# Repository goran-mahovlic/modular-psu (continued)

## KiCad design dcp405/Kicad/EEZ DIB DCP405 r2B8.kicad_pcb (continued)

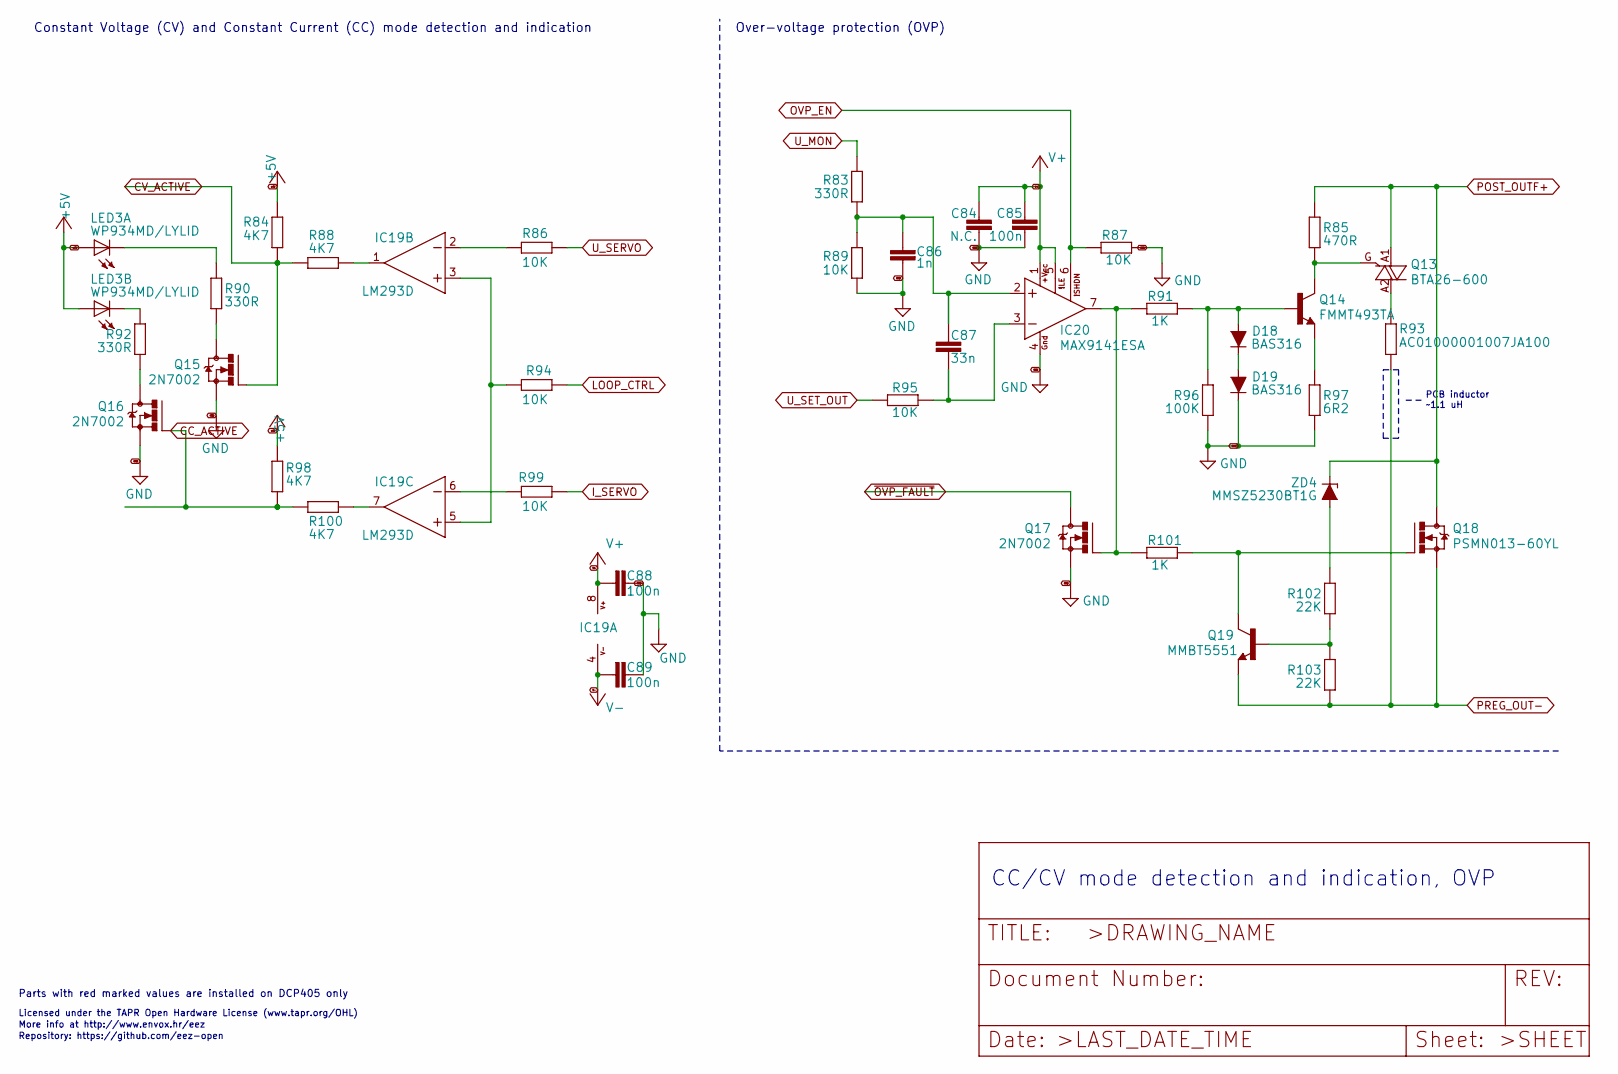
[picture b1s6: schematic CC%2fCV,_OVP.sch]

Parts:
C84: N.C.; C0805
C85, C88, C89: 100n; C0603
C86: 1n; C0805
C87: 33n; C0805
D18, D19: BAS316; SOD323-R
IC19: LM293D; SOIC127P600X173-8N
IC20: MAX9141ESA; SOIC127P600X173-8N
LED3: WP934MD/LYLID; WP934MD
Q13: BTA26-600; TOP3_TRIAC_NOHOLE
Q14: FMMT493TA; SOT23-BEC
Q15, Q16, Q17: 2N7002; SOT103P240X110-3N
Q18: PSMN013-60YL; SOT669
Q19: MMBT5551; SOT23-BEC
R83, R90, R92: 330R; R0805
R84, R88, R98, R100: 4K7; R0805
R85: 470R; R0805
R86, R87, R89, R94, R95, R99: 10K; R0805
R91, R101: 1K; R0805
R93: AC01000001007JA100; 0411_15
R96: 100K; R0805
R97: 6R2; R0805
R102, R103: 22K; R0805
ZD4: MMSZ5230BT1G; SOD123

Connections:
+5V: LED3.BA (A), LED3.TA (A), R84.2, R98.2; also elsewhere on the board
CC_ACTIVE: Q16.1 (G), R98.1, R100.2; also elsewhere on the board
CV_ACTIVE: Q15.1 (G), R84.1, R88.2; also elsewhere on the board
GND: C84.2, C85.1, C86.1, C88.1, C89.1, D19.C, IC20.4 (GND), Q15.2 (S), Q16.2 (S), Q17.2 (S), R87.1, R89.2, R96.1, R97.1; also elsewhere on the board
I_SERVO: R99.1; also elsewhere on the board
LOOP_CTRL: R94.2; also elsewhere on the board
unnamed: C86.2, C87.1, IC20.2 (+IN), R83.2, R89.1
unnamed: C87.2, IC20.3 (-IN), R95.2
unnamed: D18.A, Q14.B, R91.1, R96.2
unnamed: D18.C, D19.A
unnamed: IC19.1 (OUT), R88.1
unnamed: IC19.2 (-IN), R86.2
unnamed: IC19.3 (+IN), IC19.5 (+IN), R94.1
unnamed: IC19.6 (-IN), R99.2
unnamed: IC19.7 (OUT), R100.1
unnamed: IC20.7 (OUT), Q17.1 (G), R91.2, R101.2
unnamed: LED3.BC (C), R92.2
unnamed: LED3.TC (C), R90.1
unnamed: Q13.A2, R93.2
unnamed: Q13.G, Q14.C, R85.1
unnamed: Q14.E, R97.2
unnamed: Q15.3 (D), R90.2
unnamed: Q16.3 (D), R92.1
unnamed: Q18.4 (G), Q19.C, R101.1
unnamed: Q19.B, R102.1, R103.2
unnamed: R102.2, ZD4.A
OVP_EN: IC20.6 (~SHDN), R87.2; also elsewhere on the board
POST_OUTF+: Q13.A1, Q18.MB (D), R85.2, ZD4.C; also elsewhere on the board
PREG_OUT-: Q18.1 (S), Q18.2 (S), Q18.3 (S), Q19.E, R93.1, R103.1; also elsewhere on the board
U_MON: R83.1; also elsewhere on the board
U_SERVO: R86.1; also elsewhere on the board
U_SET_OUT: R95.1; also elsewhere on the board
V+: C84.1, C85.2, C88.2, IC19.8 (V+), IC20.1 (+VCC), IC20.5 (~LE); also elsewhere on the board
V-: C89.2, IC19.4 (V-); also elsewhere on the board
~OVP_FAULT: Q17.3 (D); also elsewhere on the board

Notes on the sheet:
Licensed under the TAPR Open Hardware License (www.tapr.org/OHL)
Repository: https://github.com/eez-open
More info at http://www.envox.hr/eez
CC/CV mode detection and indication, OVP
Constant Voltage (CV) and Constant Current (CC) mode detection and indication
Over-voltage protection (OVP)
PCB inductor ~~1.1 uH ~
Parts with red marked values are installed on DCP405 only

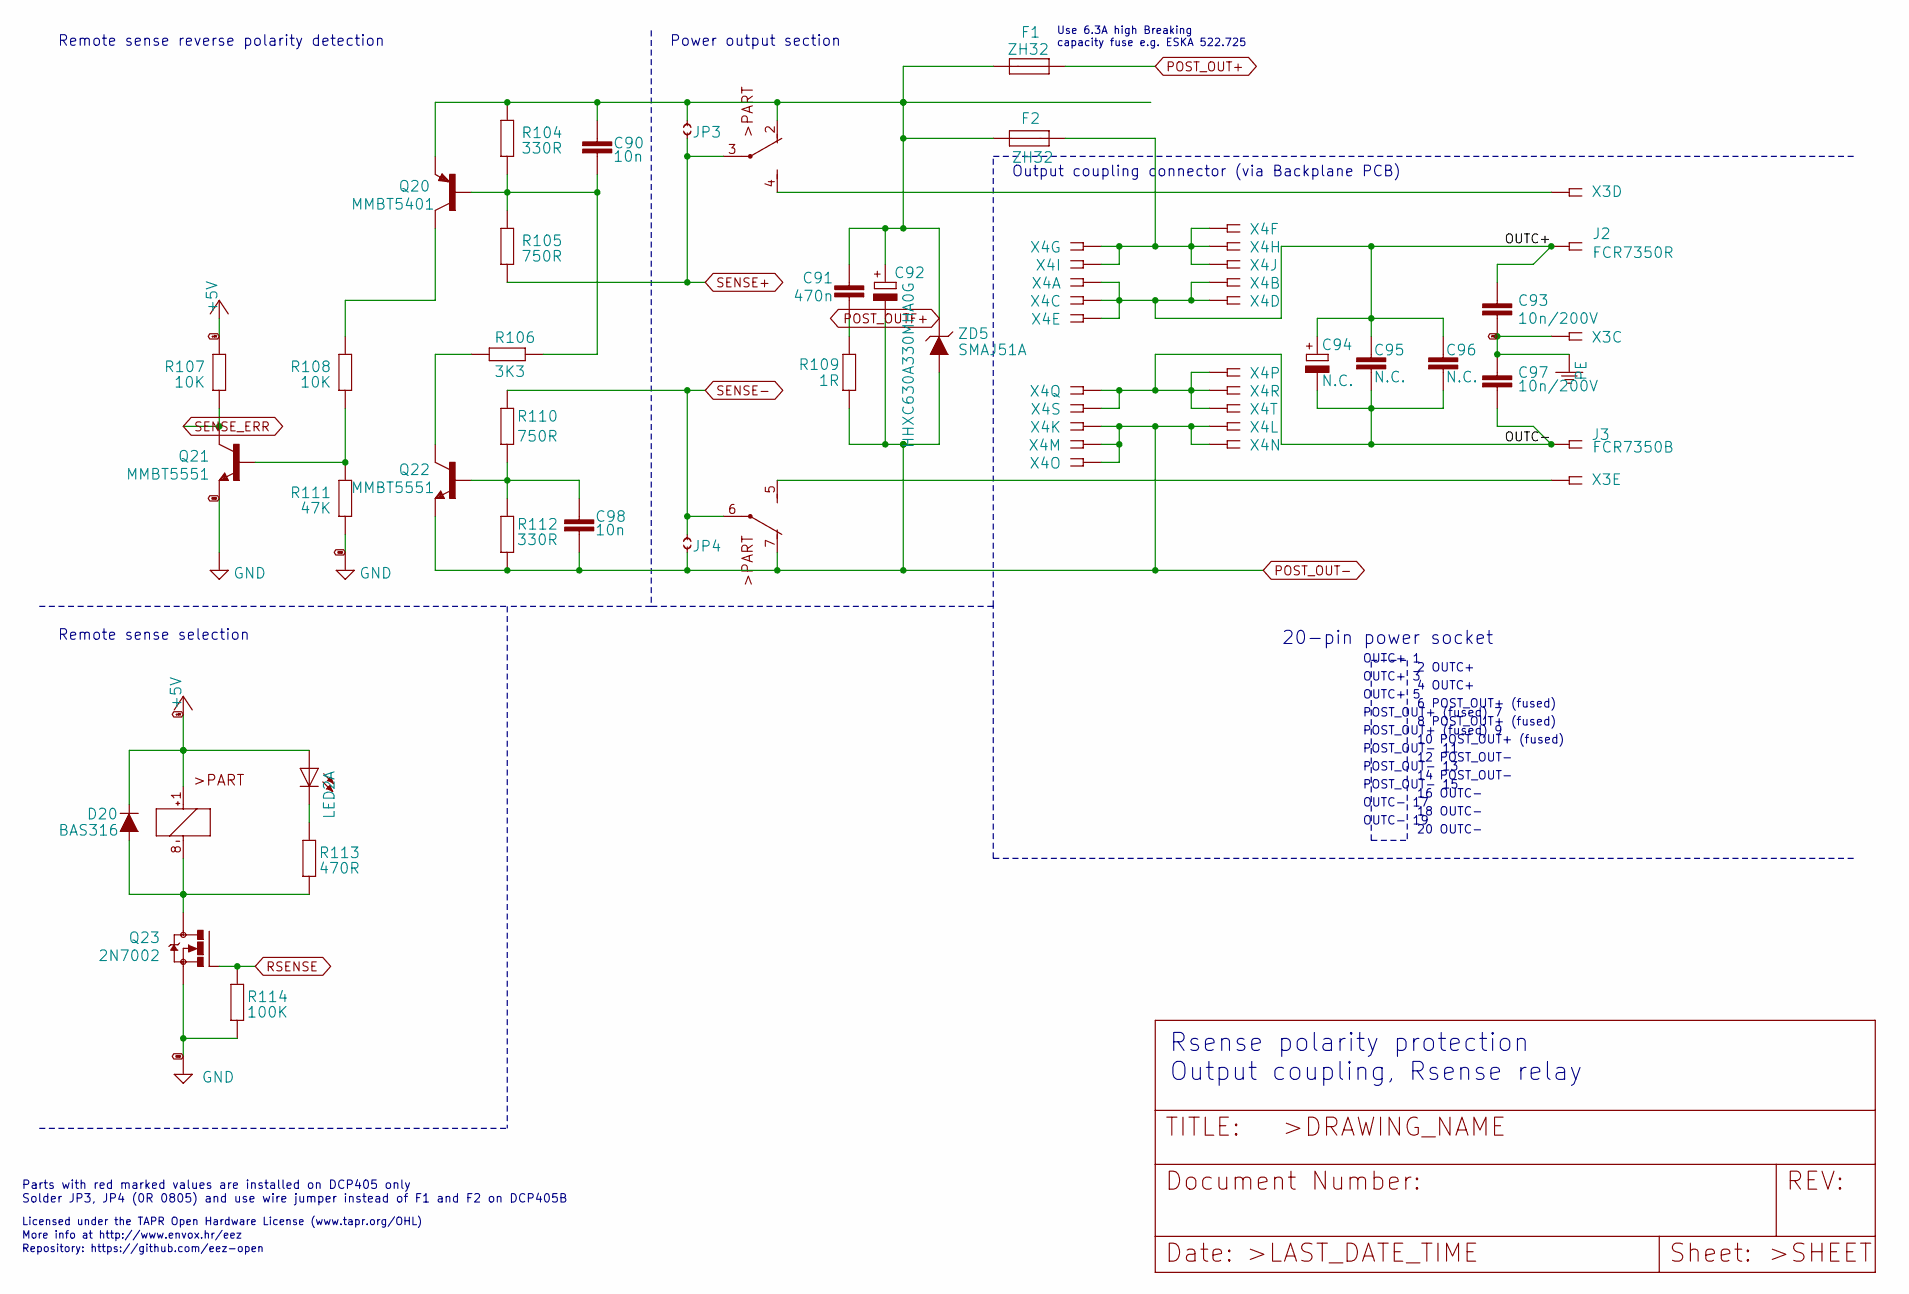
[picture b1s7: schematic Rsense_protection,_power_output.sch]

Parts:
C90, C98: 10n; C0805
C91: 470n; C0805
C92: HHXC630A330MHA0G; CAPAE830X1050N
C93, C97: 10n/200V; C1206
C94: N.C.; ECAP2_5
C95, C96: N.C.; C0805
D20: BAS316; SOD323-R
F1, F2: ZH32
J2: FCR7350R; S16N-PC
J3: FCR7350B; S16N-PC
JP3, JP4: JP2-CUT-0805; R_0805
K1: G6K-2F-5DC; G6K-2F
LED2: WP934MD/2LID; WP934MD
Q20: MMBT5401; SOT23-BEC
Q21, Q22: MMBT5551; SOT23-BEC
Q23: 2N7002; SOT103P240X110-3N
R104, R112: 330R; R0805
R105, R110: 750R; R0805
R106: 3K3; R0805
R107, R108: 10K; R0805
R109: 1R; R1206
R111: 47K; R0805
R113: 470R; R0805
R114: 100K; R0805
X3: 691322110005; MC1,5_5-G-3,5
X4: DS1024-2*10R0; SSW-110-02-T-D-RA
ZD5: SMAJ51A; DO214AA

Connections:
+5V: D20.C, K1.1 (+), LED2.TA (A), R107.2; also elsewhere on the board
/Rsense protection, power output/OUTC+: C93.1, C94.+, C95.1, C96.1, J2.1, J2.NC1, J2.NC2, J2.NC3, J2.NC4, X4.1, X4.2, X4.3, X4.4, X4.5
/Rsense protection, power output/OUTC-: C94.-, C95.2, C96.2, C97.2, J3.1, J3.NC1, J3.NC2, J3.NC3, J3.NC4, X4.16, X4.17, X4.18, X4.19, X4.20
GND: Q21.E, Q23.2 (S), R111.1, R114.1; also elsewhere on the board
unnamed: C90.2, Q20.B, R104.1, R105.2, R106.2
unnamed: C91.2, R109.2
unnamed: C98.1, Q22.B, R110.1, R112.2
unnamed: D20.A, K1.8 (-), Q23.3 (D), R113.1
unnamed: F2.2, X4.6, X4.7, X4.8, X4.9, X4.10
unnamed: K1.4 (S), X3.4
unnamed: K1.5 (S), X3.5
unnamed: LED2.TC (C), R113.2
unnamed: Q20.C, R108.2
unnamed: Q21.B, R108.1, R111.2
unnamed: Q22.C, R106.1
PE: C93.2, C97.1, X3.3; also elsewhere on the board
POST_OUT+: F1.1; also elsewhere on the board
POST_OUT-: C92.-, C98.2, JP4.1, K1.7 (O), Q22.E, R109.1, R112.1, X4.11, X4.12, X4.13, X4.14, X4.15, ZD5.A; also elsewhere on the board
POST_OUTF+: C90.1, C91.1, C92.+, F1.2, F2.1, JP3.2, K1.2 (O), Q20.E, R104.2, ZD5.C; also elsewhere on the board
RSENSE: Q23.1 (G), R114.2; also elsewhere on the board
SENSE+: JP3.1, K1.3, R105.1; also elsewhere on the board
SENSE-: JP4.2, K1.6, R110.2; also elsewhere on the board
SENSE_ERR: Q21.C, R107.1; also elsewhere on the board

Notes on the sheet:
Rsense polarity protection Output coupling, Rsense relay
Licensed under the TAPR Open Hardware License (www.tapr.org/OHL)
Repository: https://github.com/eez-open
More info at http://www.envox.hr/eez
Remote sense reverse polarity detection
Remote sense selection
POST_OUT+ (fused) 7
16 OUTC-
6 POST_OUT+ (fused)
20-pin power socket
10 POST_OUT+ (fused)
POST_OUT+ (fused) 9
2 OUTC+
12 POST_OUT-
OUTC+ 1
POST_OUT- 11
8 POST_OUT+ (fused)
OUTC+ 5
OUTC- 19
4 OUTC+
OUTC- 17
20 OUTC-
OUTC+ 3
14 POST_OUT-
POST_OUT- 15
POST_OUT- 13
18 OUTC-
Output coupling connector (via Backplane PCB)
Power output section
Use 6.3A high Breaking capacity fuse e.g. ESKA 522.725
Parts with red marked values are installed on DCP405 only Solder JP3, JP4 (0R 0805) and use wire jumper instead of F1 and F2 on DCP405B

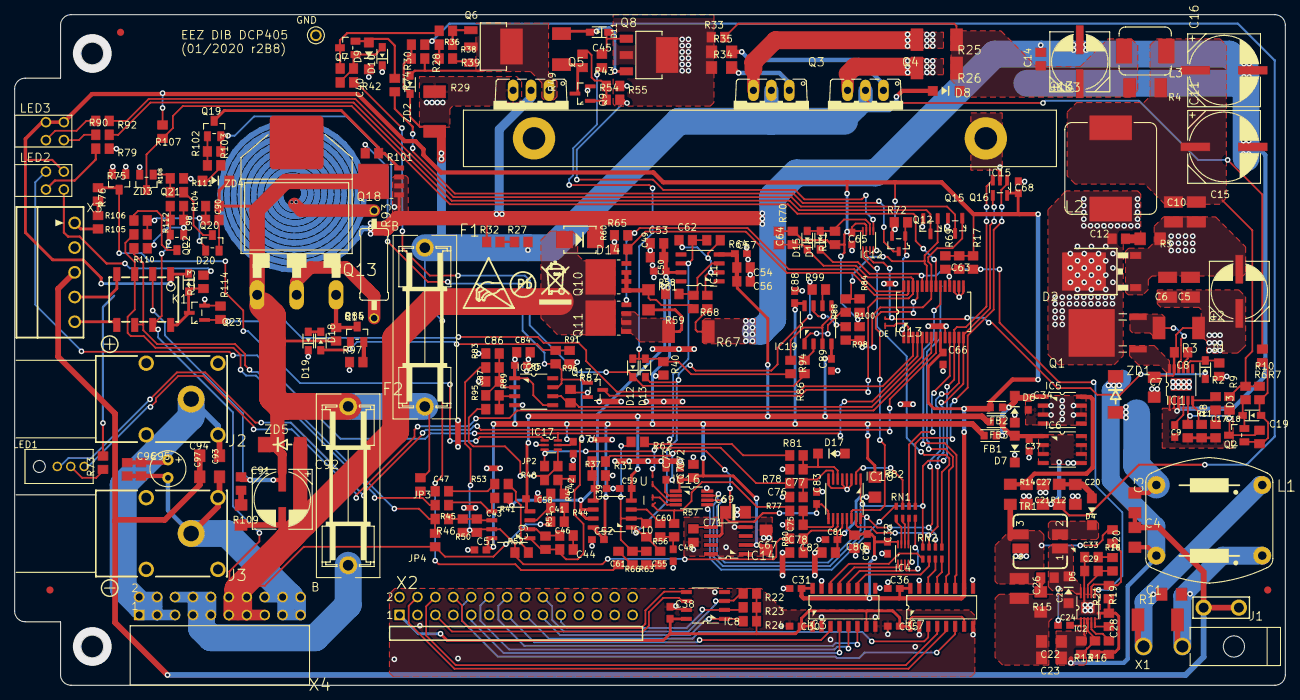
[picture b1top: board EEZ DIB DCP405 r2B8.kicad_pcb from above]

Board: 2 copper layers, 180.0 x 95.0 mm, 324 parts (0 on the bottom side), 194 nets.

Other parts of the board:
EEZ_SIGNATURE: SIGNATURESMALL; SIGNATURE_5MM
U$1: RECYCLE_BIN1_8
U$6: ESD_SYMBOL
U$7: PB_SMALL

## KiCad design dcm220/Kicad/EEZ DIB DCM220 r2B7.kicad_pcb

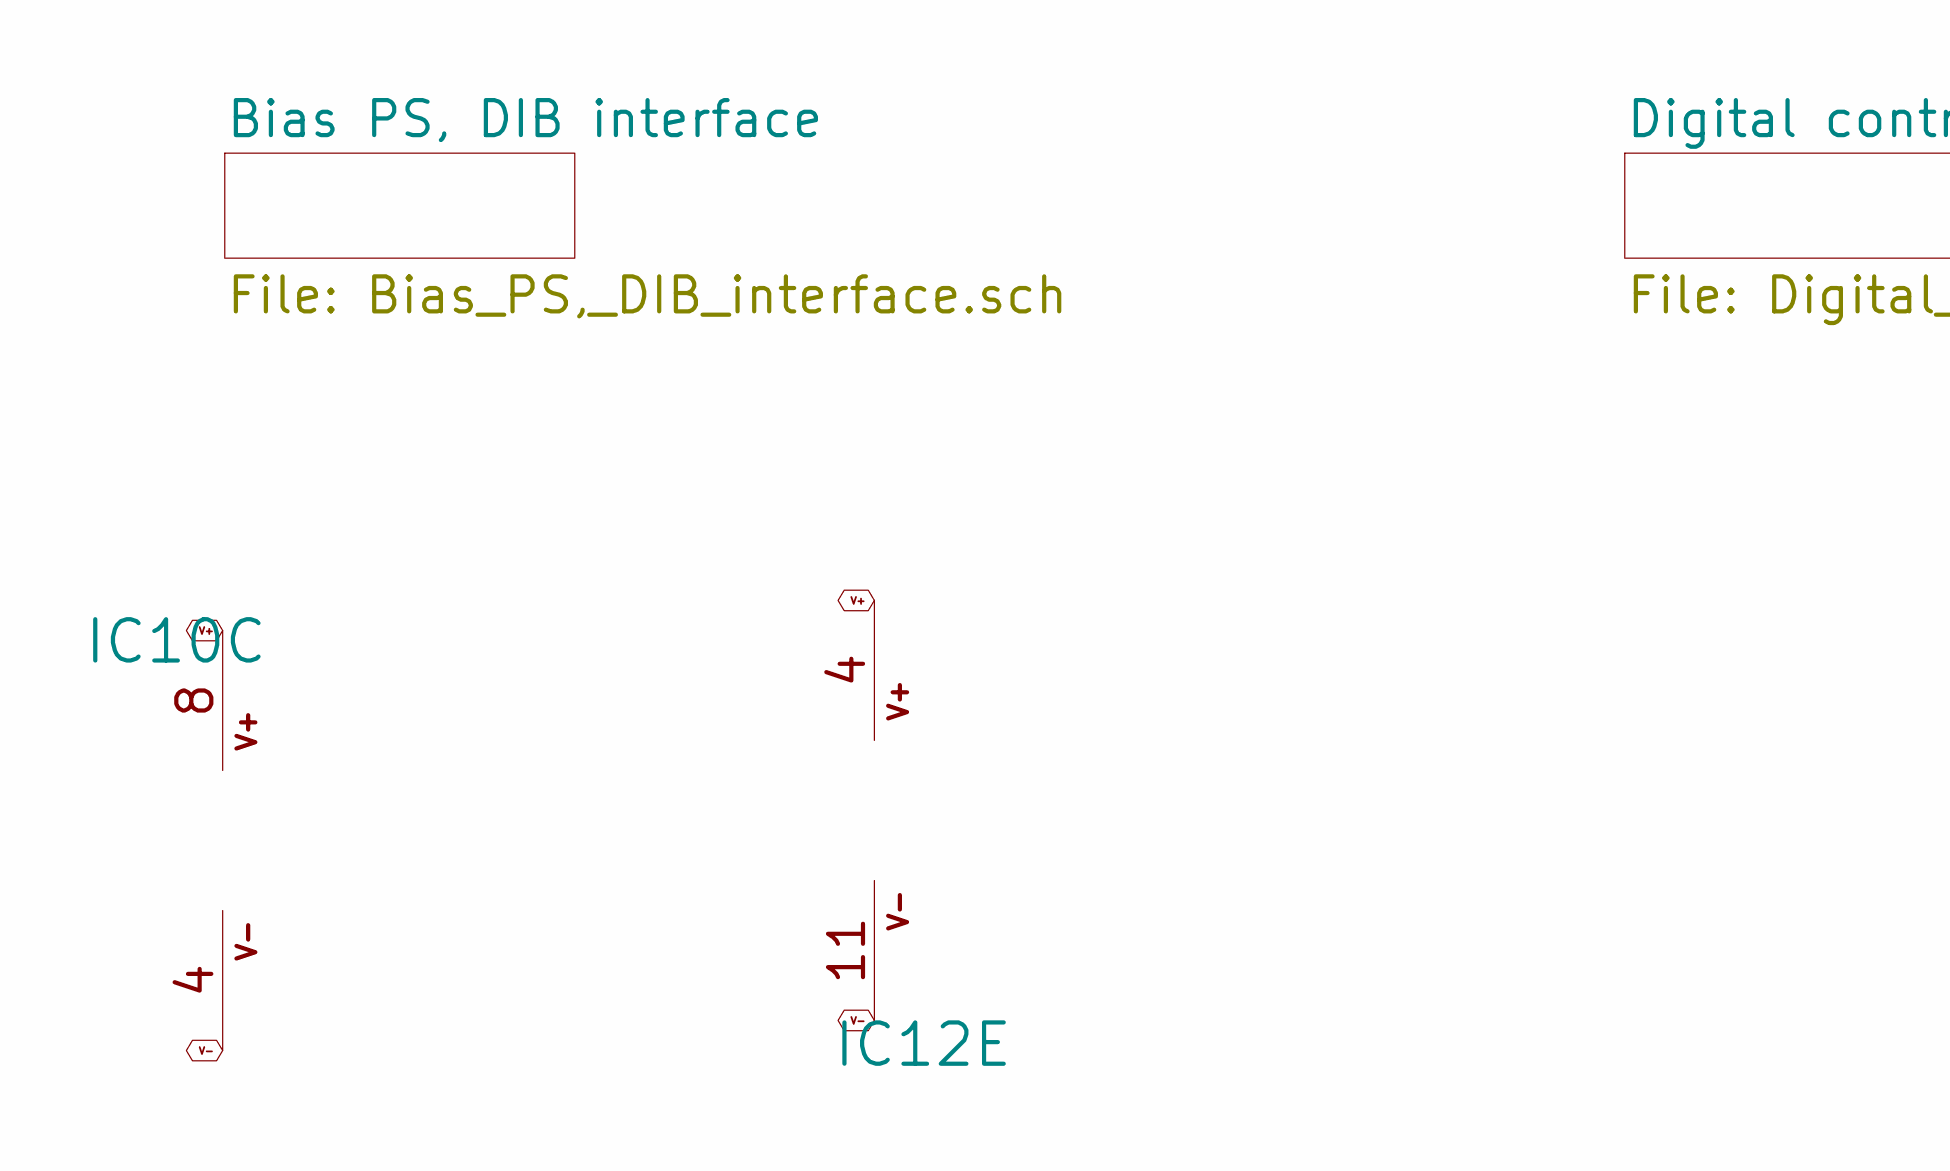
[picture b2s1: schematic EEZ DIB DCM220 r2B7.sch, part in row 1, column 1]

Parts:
IC10: MC33272ADR2G; SOIC127P600X173-8N
IC12: MC33274ADR2G; SOIC127P600X175-14N

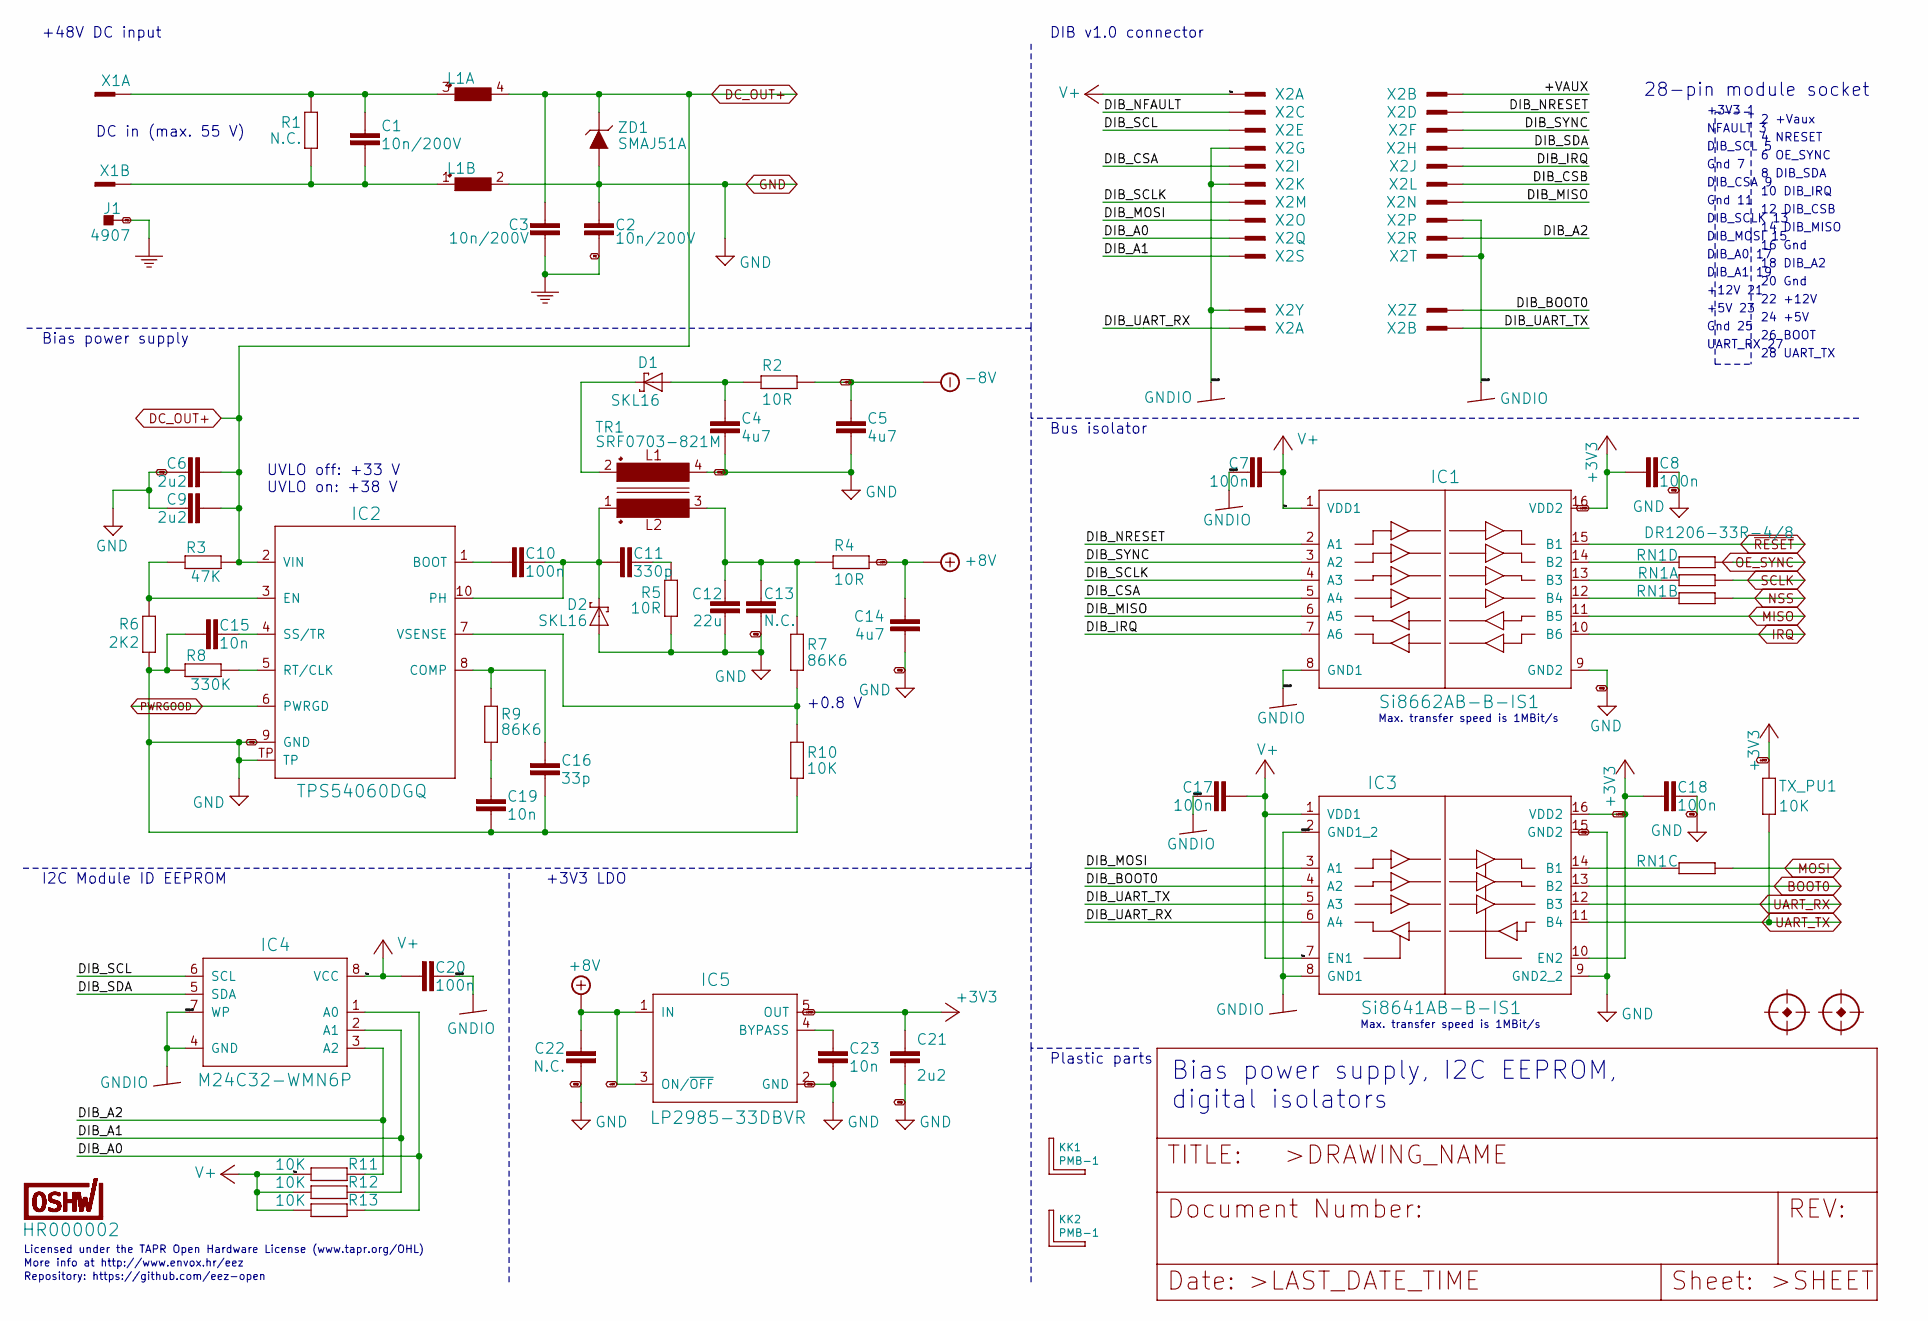
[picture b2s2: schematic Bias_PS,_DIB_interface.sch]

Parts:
C1, C2, C3: 10n/200V; C1206
C4, C5, C14: 4u7; C1206
C6, C9, C21: 2u2; C1206
C7, C8, C10, C17, C18, C20: 100n; C0603
C11: 330p; C0805
C12: 22u; C1206
C13: N.C.; C1206
C15, C19, C23: 10n; C0805
C16: 33p; C0603
C22: N.C.; C0805
D1, D2: SKL16; SOD123
FM1, FM2: FIDUCIAL_2; FIDUCIAL_DUAL
IC1: Si8662AB-B-IS1; SOIC-16
IC2: TPS54060DGQ; SOP50P490X110-11N
IC3: Si8641AB-B-IS1; SOIC-16
IC4: M24C32-WMN6P; SOIC127P600X173-8N
IC5: LP2985-33DBVR; SOT95P270X145-5N
J1: 4907; PCB_TAB-4907
KK1, KK2: PMB-1; PCB-MB
L1: RN112-4-02-0M7; RN112
R1: N.C.; R2512
R2, R4, R5: 10R; R0805
R3: 47K; R0805
R6: 2K2; R0805
R7, R9: 86K6; R0805
R8: 330K; R0805
R10, R11, R12, R13: 10K; R0805
RN1: DR1206-33R-4/8; CAY16
TR1: SRF0703-821M; SRF0703
TX_PU: 10K; R0805
U$3: HR000002; CERT-SMALL-SILK
X1: 39-30-1020; MINIFIT_39301020
X2: 77317-104-28LF
ZD1: SMAJ51A; DO214AA

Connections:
/Bias PS, DIB interface/+VAUX: X2.2
/Bias PS, DIB interface/DIB_A0: IC4.1 (A0), R13.2, X2.17
/Bias PS, DIB interface/DIB_A1: IC4.2 (A1), R12.2, X2.19
/Bias PS, DIB interface/DIB_A2: IC4.3 (A2), R11.2, X2.18
/Bias PS, DIB interface/DIB_BOOT0: IC3.4 (A2), X2.26
/Bias PS, DIB interface/DIB_CSA: IC1.5 (A4), X2.9
/Bias PS, DIB interface/DIB_CSB: X2.12
/Bias PS, DIB interface/DIB_IRQ: IC1.7 (A6), X2.10
/Bias PS, DIB interface/DIB_MISO: IC1.6 (A5), X2.14
/Bias PS, DIB interface/DIB_MOSI: IC3.3 (A1), X2.15
/Bias PS, DIB interface/DIB_NFAULT: X2.3
/Bias PS, DIB interface/DIB_NRESET: IC1.2 (A1), X2.4
/Bias PS, DIB interface/DIB_SCL: IC4.6 (SCL), X2.5
/Bias PS, DIB interface/DIB_SCLK: IC1.4 (A3), X2.13
/Bias PS, DIB interface/DIB_SDA: IC4.5 (SDA), X2.8
/Bias PS, DIB interface/DIB_SYNC: IC1.3 (A2), X2.6
/Bias PS, DIB interface/DIB_UART_RX: IC3.6 (A4), X2.27
/Bias PS, DIB interface/DIB_UART_TX: IC3.5 (A3), X2.28
BOOT0: IC3.13 (B2); also elsewhere on the board
DC_OUT+: C3.2, C6.1, C9.1, IC2.2 (VIN), L1.4 (2), R3.2, ZD1.C; also elsewhere on the board
GNDIO: C7.2, C17.2, C20.1, IC1.8 (GND1), IC3.2 (GND1_2), IC3.8 (GND1), IC4.4 (GND), IC4.7 (WP), X2.7, X2.11, X2.16, X2.20, X2.25
IRQ: IC1.10 (B6); also elsewhere on the board
MISO: IC1.11 (B5); also elsewhere on the board
MOSI: RN1.5 (2); also elsewhere on the board
NSS: RN1.6 (2); also elsewhere on the board
unnamed: C1.1, L1.1, R1.1, X1.2
unnamed: C1.2, L1.3 (1), R1.2, X1.1
unnamed: C4.1, D1.A, R2.2
unnamed: C10.1, C11.1, D2.C, IC2.10 (PH), TR1.1
unnamed: C10.2, IC2.1 (BOOT)
unnamed: C11.2, R5.2
unnamed: C12.1, C13.1, R4.2, R7.2, TR1.3
unnamed: C15.1, IC2.4 (SS/TR)
unnamed: C16.2, IC2.8 (COMP), R9.2
unnamed: C19.2, R9.1
unnamed: C23.2, IC5.4 (BYPASS)
unnamed: D1.C, TR1.2
unnamed: IC1.12 (B4), RN1.3 (1)
unnamed: IC1.13 (B3), RN1.2 (1)
unnamed: IC1.14 (B2), RN1.1
unnamed: IC2.3 (EN), R3.1, R6.2
unnamed: IC2.5 (RT/CLK), R8.2
unnamed: IC2.7 (VSENSE), R7.1, R10.2
unnamed: IC3.14 (B1), RN1.4 (1)
OE_SYNC: RN1.8 (2); also elsewhere on the board
PE: C2.2, C3.1, J1.1, J1.2; also elsewhere on the board
PWRGOOD: IC2.6 (PWRGD); also elsewhere on the board
SCLK: RN1.7 (2); also elsewhere on the board
UART_RX: IC3.12 (B3); also elsewhere on the board
UART_TX: IC3.11 (B4), TX_PU.1; also elsewhere on the board
~RESET: IC1.15 (B1); also elsewhere on the board

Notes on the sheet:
Licensed under the TAPR Open Hardware License (www.tapr.org/OHL)
Repository: https://github.com/eez-open
More info at http://www.envox.hr/eez
I2C Module ID EEPROM
Bias power supply, I2C EEPROM, digital isolators
Plastic parts
26 BOOT
Gnd 7
22 +12V
16 Gnd
6 OE_SYNC
24 +5V
+5V 23
Gnd 25
28-pin module socket
+12V 21
10 DIB_IRQ
DIB_CSA 9
2 +Vaux
12 DIB_CSB
+3V3 1
Gnd 11
8 DIB_SDA
DIB_SCL 5
DIB_A1 19
4 NRESET
DIB_A0 17
20 Gnd
NFAULT 3
14 DIB_MISO
DIB_MOSI 15
DIB_SCLK 13
18 DIB_A2
DC in (max. 55 V)
Bus isolator
+0.8 V
UART_RX 27
28 UART_TX
UVLO off: +33 V UVLO on: +38 V
+3V3 LDO

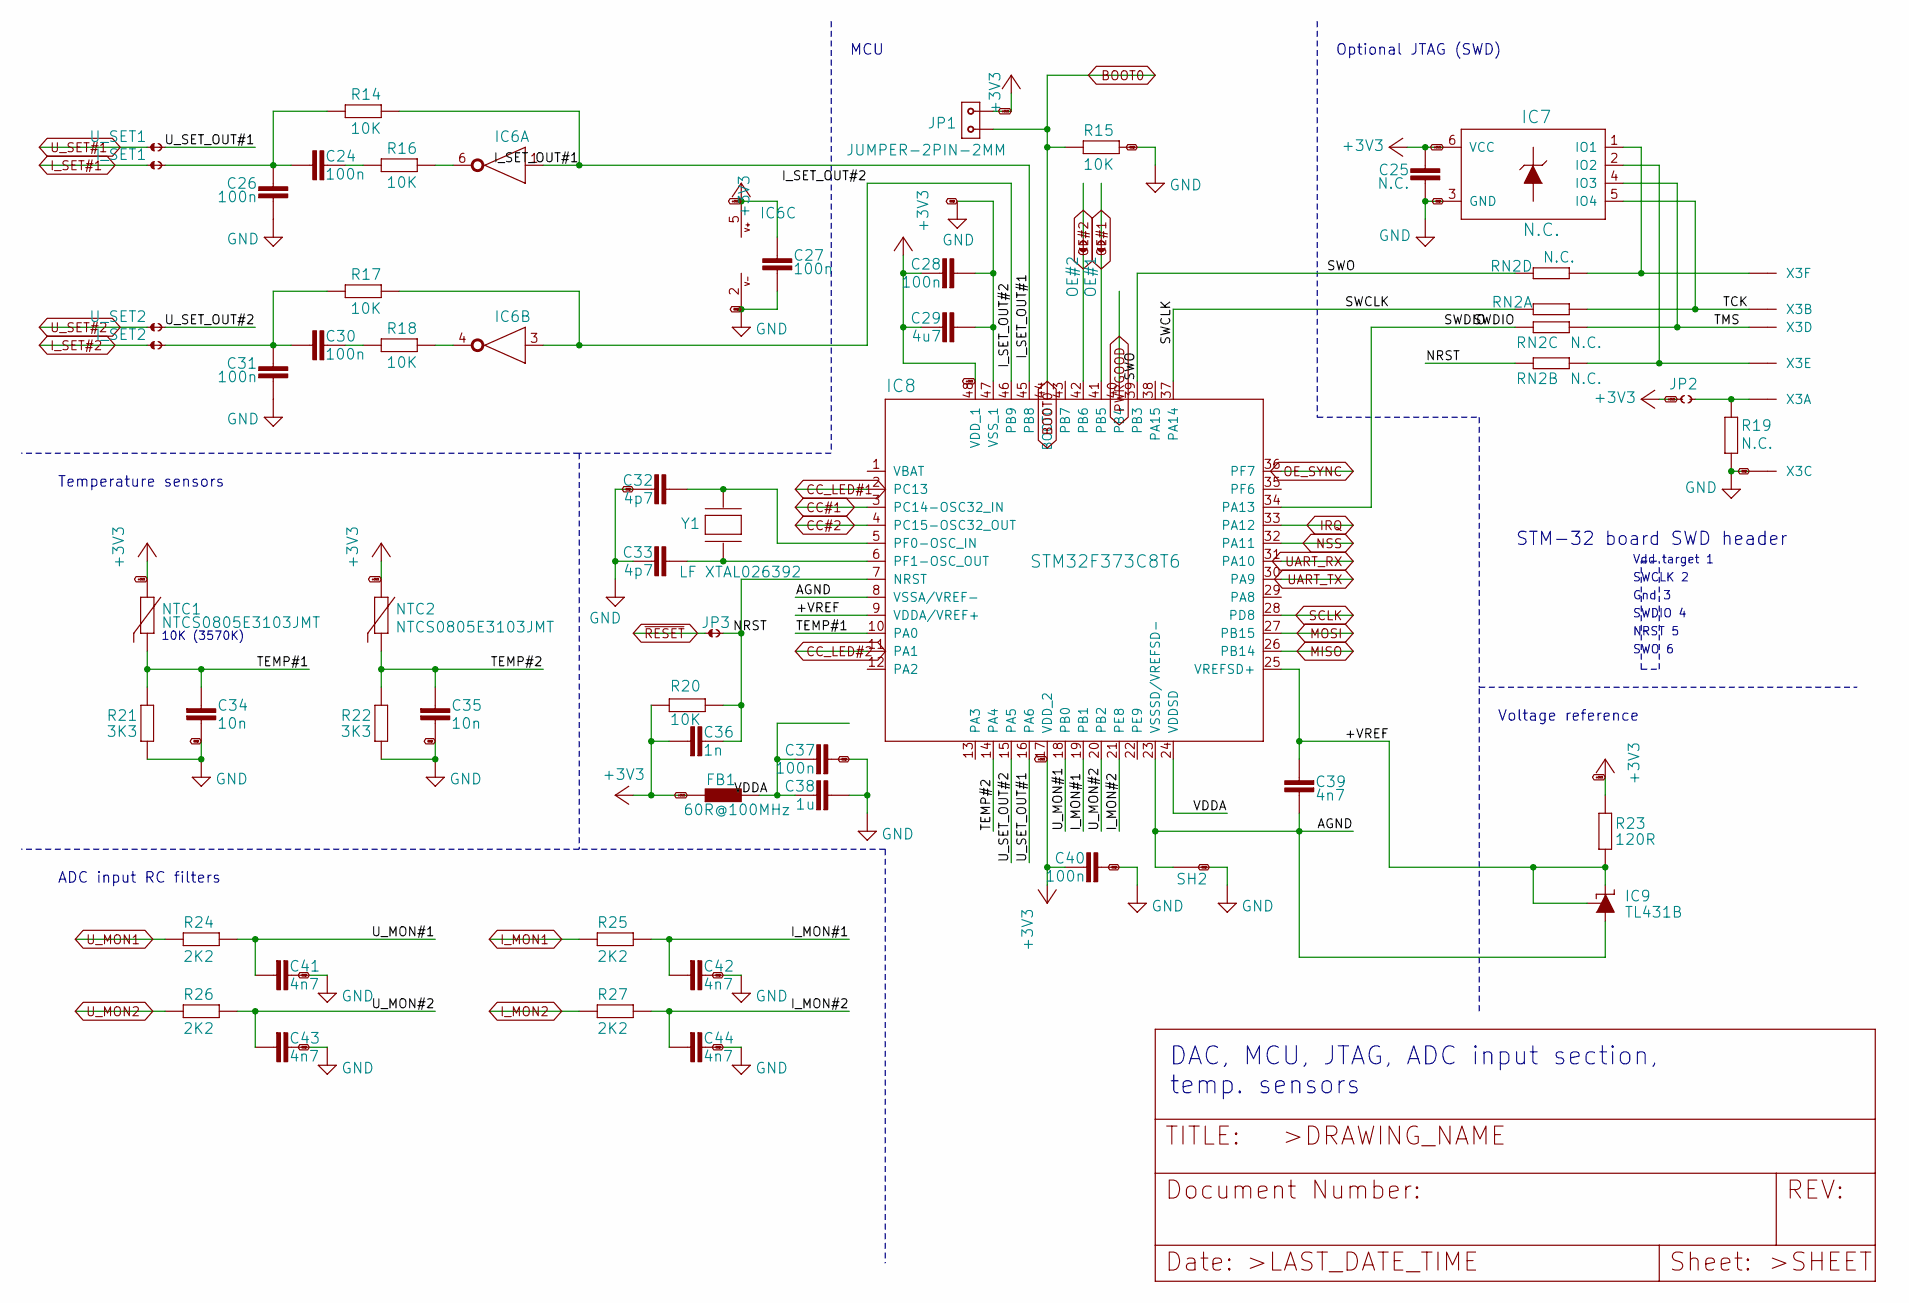
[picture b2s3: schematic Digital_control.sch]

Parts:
C24, C26, C27, C28, C30, C31, C37, C40: 100n; C0603
C25: N.C.; C0603
C29: 4u7; C1206
C32, C33: 4p7; C0603
C34, C35: 10n; C0805
C36: 1n; C0805
C38: 1u; C0805
C39, C41, C42, C43, C44: 4n7; C0805
FB1: 60R@100MHz; BEAD0603
IC6: 74HC2G04GW,125; SOT65P210X110-6N
IC7: N.C.; DRL6
IC8: STM32F373C8T6; LQFP-48
IC9: TL431B; SOT103P240X110-3N
I_SET1, I_SET2: JP2-NOCUT
JP1: JUMPER-2PIN-2MM; 2MM-2
JP2: JP2-CUT
JP3: JP2-NOCUT
NTC1, NTC2: NTCS0805E3103JMT; R_0805
OE#1, OE#2: JP2-NOCUT
R14, R15, R16, R17, R18, R20: 10K; R0805
R19: N.C.; R0805
R21, R22: 3K3; R0805
R23: 120R; R0805
R24, R25, R26, R27: 2K2; R0805
RN2: N.C.; CAY16
SH2: SHORTNOHOLE; SHORT_NOHOLE
U_SET1, U_SET2: JP2-NOCUT
X3: N.C.; 22-23-2061
Y1: LF XTAL026392; 12SMX(B)

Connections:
/Digital control/+VREF: C39.2, IC8.9 (VDDA/VREF+), IC8.25 (VREFSD+), IC9.1 (C), IC9.2 (R), R23.2
/Digital control/AGND: C39.1, IC8.8 (VSSA/VREF-), IC8.23 (VSSSD/VREFSD-), IC9.3 (A), SH2.1 (GND_A)
/Digital control/I_MON#1: C42.2, IC8.19 (PB1), R25.1
/Digital control/I_MON#2: C44.2, IC8.21 (PE8), R27.1
/Digital control/I_SET_OUT#1: IC6.1 (I), IC8.45 (PB8), R14.2
/Digital control/I_SET_OUT#2: IC6.3 (I), IC8.46 (PB9), R17.2
/Digital control/NRST: C36.1, IC8.7 (NRST), JP3.2, R20.2, RN2.3 (1)
/Digital control/SWCLK: IC8.37 (PA14), RN2.2 (1)
/Digital control/SWDIO: IC8.34 (PA13), RN2.4 (1)
/Digital control/SWO: IC8.39 (PB3), RN2.1
/Digital control/TCK: IC7.5 (IO4), RN2.7 (2), X3.2
/Digital control/TEMP#1: C34.2, IC8.10 (PA0), NTC1.2, R21.1
/Digital control/TEMP#2: C35.2, IC8.14 (PA4), NTC2.2, R22.1
/Digital control/TMS: IC7.4 (IO3), RN2.5 (2), X3.4
/Digital control/U_MON#1: C41.2, IC8.18 (PB0), R24.1
/Digital control/U_MON#2: C43.2, IC8.20 (PB2), R26.1
/Digital control/U_SET_OUT#1: IC8.16 (PA6), U_SET1.2
/Digital control/U_SET_OUT#2: IC8.15 (PA5), U_SET2.2
/Digital control/VDDA: C37.2, C38.2, FB1.P$2 (2), IC8.24 (VDDSD)
BOOT0: IC8.44 (BOOT0), JP1.2, R15.2; also elsewhere on the board
CC#1: IC8.3 (PC14-OSC32_IN); also elsewhere on the board
CC#2: IC8.4 (PC15-OSC32_OUT); also elsewhere on the board
CC_LED#1: IC8.2 (PC13); also elsewhere on the board
CC_LED#2: IC8.11 (PA1); also elsewhere on the board
IRQ: IC8.33 (PA12); also elsewhere on the board
I_MON1: R25.2; also elsewhere on the board
I_MON2: R27.2; also elsewhere on the board
I_SET#1: I_SET1.1; also elsewhere on the board
I_SET#2: I_SET2.1; also elsewhere on the board
MISO: IC8.26 (PB14); also elsewhere on the board
MOSI: IC8.27 (PB15); also elsewhere on the board
NSS: IC8.32 (PA11); also elsewhere on the board
unnamed: C24.1, C26.1, I_SET1.2, R14.1
unnamed: C24.2, R16.1
unnamed: C30.1, C31.1, I_SET2.2, R17.1
unnamed: C30.2, R18.1
unnamed: C32.2, IC8.5 (PF0-OSC_IN), Y1.3 (2)
unnamed: C33.2, IC8.6 (PF1-OSC_OUT), Y1.1
unnamed: IC6.4 (O), R18.2
unnamed: IC6.6 (O), R16.2
unnamed: IC7.1 (IO1), RN2.8 (2), X3.6
unnamed: IC7.2 (IO2), RN2.6 (2), X3.5
unnamed: IC8.41 (PB5), OE#1.1
unnamed: IC8.42 (PB6), OE#2.1
unnamed: JP2.2, R19.2, X3.1
OE#1: OE#1.2; also elsewhere on the board
OE#2: OE#2.2; also elsewhere on the board
OE_SYNC: IC8.36 (PF7); also elsewhere on the board
PWRGOOD: IC8.40 (PB4); also elsewhere on the board
SCLK: IC8.28 (PD8); also elsewhere on the board
UART_RX: IC8.31 (PA10); also elsewhere on the board
UART_TX: IC8.30 (PA9); also elsewhere on the board
U_MON1: R24.2; also elsewhere on the board
U_MON2: R26.2; also elsewhere on the board
U_SET#1: U_SET1.1; also elsewhere on the board
U_SET#2: U_SET2.1; also elsewhere on the board
~RESET: JP3.1; also elsewhere on the board

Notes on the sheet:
DAC, MCU, JTAG, ADC input section, temp. sensors
SWDIO 4
SWCLK 2
Vdd target 1
STM-32 board SWD header
Gnd 3
NRST 5
SWO 6
Optional JTAG (SWD)
MCU
10K (3570K)
Temperature sensors
ADC input RC filters
Voltage reference
